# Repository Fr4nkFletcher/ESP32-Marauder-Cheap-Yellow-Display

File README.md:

# Marauder 1.4.3 for CYD 4.0" E32R40T

- Add support for ESP32-4848S040 4.0" ST7796/XPT2046 Resistive Touch (E32R40T)
- Portrait and landscape touch calibration measured on E32R40T hardware
- CYD_40 set as the default active board
- Add `User_Setup_cyd40.h` TFT_eSPI configuration for CYD_40

---

## Requirements

1. A compatible CYD module (see [Compatibility](#compatibility) section below)
2. A data-capable USB cable
3. *(Optional)* GPS module for enhanced functionality — https://github.com/justcallmekoko/ESP32Marauder/wiki/gps-modification

---

## Installation

### Option 1 — esptool.py (Recommended)

Flash directly from the prebuilt binaries in this repo.

Install esptool if you don't have it:

```
pip install esptool
```

Flash:

```
esptool.py --port /dev/YOURSERIALPORT write_flash \
  0x1000  bins/esp32_marauder.ino.bootloader.bin \
  0x8000  bins/esp32_marauder.ino.partitions.bin \
  0x10000 bins/esp32_marauder_v1_4_3_20260627_cyd40_nogps.bin
```

Replace the firmware filename with `cyd40_gps.bin` if you have a GPS module wired up.

#### Troubleshooting:

1. Unplug and restart your CYD module
2. Hold `RST`, tap `BOOT`, release `RST` (the screen should go blank)
3. Re-run the flash command

---

### Option 2 — Arduino IDE (Build from Source)

1. Set up your Arduino environment following the [ESP32 Marauder Arduino IDE Setup Guide](https://github.com/justcallmekoko/ESP32Marauder/wiki/arduino-ide-setup)
2. Update your platform.txt
3. Add the necessary libraries to your Arduino libraries folder
4. Set the upload speed to `115200`
5. In `configs.h`, uncomment the `#define` for your board (default is `CYD_40`)
6. Upload to your CYD module

---

## Compatibility

The following boards are supported. The **4.0" E32R40T** is the default in this fork — for any other board, comment out `#define CYD_40` in `configs.h` and uncomment your board's define.

- **[4.0" Resistive Touch E32R40T](https://www.amazon.com/dp/B0FGJJ24S1)** ← default in this fork
- [1.9" ESP32-S3 No Touch](https://www.aliexpress.us/item/3256807423694742.html)
- [2.4" Capacitive Touch](https://a.co/d/bTSoo9Z)
- [2.4" Resistive Touch](https://a.co/d/fhM7s0J)
- [2.4" Resistive Touch Guition](https://www.aliexpress.us/item/3256806436471011.html)
- [2.8" Resistive MicroUSB-only](https://amazon.com/dp/B0BVFXR313)
- [2.8" Resistive MicroUSB/Type-C 2USB](https://amazon.com/dp/B0CLR7MQ91)
- [3.2" Resistive Touch](https://www.aliexpress.us/item/3256806436888726.html)
- [3.2" Capacitive Touch](https://a.co/d/faB7oVU)
- [3.5" Resistive Touch](https://a.co/d/cxUc73a)
- [3.5" Capacitive Touch](https://a.co/d/2PFDlvL)

No hardware modifications required.

---

## GPS Functionality

GPS is supported via the 4-pin connector near the MicroUSB port. For compatible hardware, refer to the [official wiki](https://github.com/justcallmekoko/ESP32Marauder/wiki/gps-modification).

| GPS | -> | CYD |
|-----|:--:|-----|
| VCC | -> | VIN |
| GND | -> | GND |
| TX  | -> | TX  |
| RX  | -> | RX  |

Note: On 2.4" and 3.5" models swap RX/TX

---

## Example Usage

After flashing, you'll boot into the Marauder interface. Refer to the [ESP32 Marauder Wiki](https://github.com/justcallmekoko/ESP32Marauder/wiki) for detailed usage instructions.

---

## Disclaimer

This project is for educational purposes only. Always obtain proper authorization before testing on networks you don't own or have explicit permission to test.

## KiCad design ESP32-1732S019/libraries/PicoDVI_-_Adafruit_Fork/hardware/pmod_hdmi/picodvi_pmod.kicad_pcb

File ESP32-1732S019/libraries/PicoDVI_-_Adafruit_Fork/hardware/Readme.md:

PicoDVI Hardware
================

This directory contains schematics and layout files

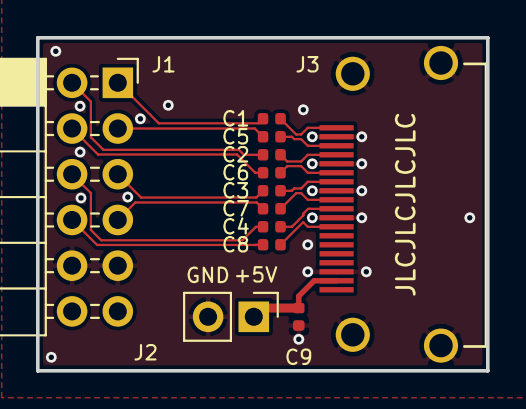
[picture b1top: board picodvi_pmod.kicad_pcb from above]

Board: 2 copper layers, 25.0 x 18.5 mm, 12 parts (0 on the bottom side), 19 nets.

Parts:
C1, C2, C3, C4, C5, C6, C7, C8, C9: 220n; C_0402_1005Metric
J1: 02x06; PinSocket_2x06_P2.54mm_Horizontal
J2: Conn_01x02; PinHeader_1x02_P2.54mm_Vertical
J3: HDMI_A; HDMI-SS-53000

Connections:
+3V3: J1.11, J1.12
+5V: C9.2, J2.1, J3.18
/CK+: C4.1, J3.10
/CK-: C8.1, J3.12
/D0+: C3.1, J3.7
/D0-: C7.1, J3.9
/D1+: C2.1, J3.4
/D1-: C6.1, J3.6
/D2+: C1.1, J3.1
/D2-: C5.1, J3.3
/PMOD_CK+: C4.2, J1.6
/PMOD_CK-: C8.2, J1.8
/PMOD_D0+: C3.2, J1.5
/PMOD_D0-: C7.2, J1.7
/PMOD_D1+: C2.2, J1.2
/PMOD_D1-: C6.2, J1.4
/PMOD_D2+: C1.2, J1.1
/PMOD_D2-: C5.2, J1.3
GND: C9.1, J1.9, J1.10, J2.2, J3.2, J3.5, J3.8, J3.11, J3.17, J3.SH

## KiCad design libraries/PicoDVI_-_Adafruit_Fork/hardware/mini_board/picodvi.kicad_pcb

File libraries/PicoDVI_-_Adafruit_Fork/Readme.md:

PicoDVI - Adafruit Fork for Arduino IDE + Adafruit_GFX compatibility
====================================================================
(Original Readme content follows later)

Implements a few framebuffer types to which Adafruit_GFX drawing operations
can be made; not every permutation PicoDVI is capable of, but a useful subset.

WARNING: all video modes require overclocking (performed automatically at
run-time, nothing to select), occasionally over-volting (optionally selected
in sketch code), and higher resolutions may require reducing the QSPI clock
rate (Tools menu in future arduino-pico release). The RP2040 microcontroller
is being run WAY beyond spec and there is a VERY SMALL BUT NONZERO
POSSIBILITY OF PERMANENT DAMAGE. Please see LICENSE file; usual software
disclaimers about liability apply, user accepts risk.

Requires Earle Philhower III RP2040 Arduino core (not the "official" Arduino
RP2040 core).

Changes vs main PicoDVI repo:
- Add library.properties file, src and examples directories per Arduino
requirements.
- A full copy of software/libdvi is made in src (originally was soft-linked but Arduino Library Manager does not approve). If any updates are made in the original PicoDVI libdvi directory, copy them here!
- The file dvi_serialiser.pio.h, normally not part of the distribution and
generated during the Pico SDK build process, is provided here for Arduino
build to work. If any changes are made in dvi_serialiser.pio (either here
or by bringing in updates from upstream code), this header will need to be
regenerated.
- extern "C" around most function defs, to be linkable with C++ (Arduino).
- A couple compile-time constants have been changed to run-time configurable
because some color and resolution things aren't known until a constructor is
called: dvi_vertical_repeat and dvi_monochrome_tmds.
- DVI_1BPP_BIT_REVERSE is switched '1' by default (to work with bit order
used by GFXcanvas1 object). Pico SDK-built examples using 1-bit mode are
fixed by changing the corresponding CMakeLists.txt files to set this to 0.
Font data has had bit order reversed to match this layout.

All files from the PicoDVI repo are kept even if not used in this build
(e.g. apps and assets directories, among others) so same repo can still be
used via Pico SDK if desired.

Original Readme content:
=======
RP2350 PicoDVI Preview
======================

Changes from the public GitHub version:

* All Arm assembly in `libdvi` has been ported to RISC-V and tuned for Hazard3
* Some of the existing Arm assembly in `libdvi` has been tweaked for better performance on Cortex-M33
* RGB encode now uses the SIO TMDS encoders by default on RP2350 (can be disabled by defining `DVI_USE_SIO_TMDS_ENCODE=0` -- see `software/libdvi/dvi_config_defs.h`)
* Much of the Arm assembly in `libsprite` has been ported to RISC-V -- enough to run the stock demos

Build instructions:

```bash
cd software
mkdir build
# PICO_PLATFORM can also be rp2350-riscv
# List of DVI configs is in software/include/common_dvi_pin_configs.h
cmake -DPICO_SDK_PATH=/path/to/sdk -DPICO_PLATFORM=rp2350 -DPICO_COPY_TO_RAM=1 -DDVI_DEFAULT_SERIAL_CONFIG=pico_sock_cfg ..
make -j$(nproc)
# Then flash a binary, e.g.:
cp apps/tiles_and_sprites/tiles_and_sprites.uf2
```

If you plan to run the `vista` demo, then note that there are now two UF2 data files, `software/assets/vista_data_rp2040.uf2` and `software/assets/vista_data_rp2350.uf2`. The only difference is the family IDs: the first can be dragged on RP2040 and on RP2350 A0, and the second can be dragged on RP2350 A1 and later.

The following is the original RP2040 writeup:

Bitbanged DVI on the RP2040 Microcontroller
===========================================

*640x480 RGB565 image, 640x480p 60 Hz DVI mode. 264 kB SRAM, 2x Cortex-M0+, system clock 252 MHz*

Quick links:

[Board Schematic](hardware/board/picodvi.pdf)

[Software Readme and Example Photos](software/)

About this Project
-----------------

This project stems from a stupid idea I had during RP2040 bringup. I couldn't convince myself the idea was too stupid to work, so I took a leap of faith on it, and the results are documented here.

RP2040 was designed to run at 133 MHz, but we found (without too much surprise) that typical silicon can be pushed further. In fact, there was overlap between the maximum system clock, and the TMDS bit clocks of slower DVI video modes. We had done great stuff with VGA on the FPGA platform, which ran at 48 MHz, but wouldn't it be absurd and wonderful to connect your microcontroller straight to an HD TV with no other electronics in between? This seemed unlikely to work out, but I stayed up at night playing around with assembly loops, and I could not convince myself that DVI was out of reach. Everything seemed to fit:

- With some of the core-local hardware on RP2040, and a neat encoding trick, I could do pixel-doubled TMDS encode on-the-fly using around 60% of an M0+ (running at 252 MHz, for 640x480p 60 Hz DVI)
- PIO can yeet out data streams at system clock frequency, and drive a 1/10th rate clock on the side, with pretty minimal programming
- Some of the DMA features are help with putting together the sync/blanking patterns on the fly, rather than having the patterns flat in memory
- With the second processor utterly unencumbered, you can render some pretty graphics to put on your DVI display. There is even enough RAM for a QVGA framebuffer!

The greatest unknown was driving 252 Mbps serial through the general-purpose digital pads (especially *differential* serial, emulated with two single-ended pads). By this point I was utterly driven and consumed by the need to find out if DVI could work, so I laid out a board over a few evenings after work.

The Rev A board uses a slightly cursed coupling circuit I first saw (and used) on the ULX3S FPGA board, which just connects 3V3 IOs straight into the HDMI socket through some coupling caps.

Those who understand the TMDS physical layer are probably screaming, but I was fine, because I did not read the electrical section of the spec until after I got this board working. Then I screamed. Before the boards arrived I did some debugging, with these two strategies:

- Run the entire system at 12 MHz (crystal freq), so that the signals are probeable, but the relative speed of IO, DMA and CPUs is the same. This makes sure my code can keep the PIO state machines fed with data
- Swap in an alternate PIO program which outputs 10 bit UART data frames instead of direct serial (a 17% drop in throughput). I could then dump the TMDS stream with a logic analyser, and examine and parse it on my machine

I also tried out my slightly harebrained TMDS encoding scheme, which matches the letter but not the spirit of the DVI specification, on an FPGA board with some DVI gateware I wrote for a previous weekend project. This confirmed that the principle was sound, and that my TV and monitor would have no trouble with the output of the matching software encoder on RP2040, provided the chip could physically shove bits out of the pins fast enough.

Because this is a home project, I didn't touch the HDL sim, and stuck to ARM debug, UART and logic analyser for my debugging. This worked some kinks out of the software, and bringup of the freshly-soldered board was smooth. After swapping the blue and red lanes into the right order -- to which I will say, in my defense, I _consistently_ thought the blue+sync lane was lane 2 -- I had a clean RGB565 QVGA 60 Hz static image on my monitor.

Improved Output Circuit
-----------------------

After reading the TMDS electrical section of the DVI spec, and staring quietly out the window for a while, wondering how this board *ever* worked, I rethought the output circuit. Eight capacitors was clearly not the way to go -- what I really needed was eight *resistors*. That's what I call a DVI PHY.

I also revised my earlier approach of "turn all the GPIOs up to 11", and reduced the pad drive and slew. At work on Monday, a colleague agreed it would be a great idea to plug my microcontroller monstrosity into the scope setup we use for 4k HDMI testing. Here are the results at VGA 60 Hz (252 Mbps):

I was sitting on the other side of the lab while he was running the test, and when the eye mask appeared he just said "do you wanna see something funny".

A clean bill of health! We also tried 720p30 (372 Mbps), which requires overvoltage on typical silicon (something you can do with one register write on RP2040):

Honestly, this has shaken me. This is a silly amount of bandwidth for a tiny little microcontroller.

Although it passes the eye mask and a few other tests, this circuit is not fully compliant with the DVI spec. In particular, our logic `1` is not quite right, due to the CMOS drive on the GPIOs: any more than a \~60 mV mismatch between the Source and Sink +3V3 rails will push our high-level offset outside of the +- 10 mV allowed by the spec. This is a real nitpick, because a *differential* receiver is unlikely to care about a 10 mV *commmon mode* offset, but still -- it is out of spec. A better circuit could use a fast Si diode and a smaller resistor value, e.g. 220 ohm, so that the emulated CML output floats on the sink's +3V3 supply when we output our 3V3 CMOS high level, but still sinks the requisite 10 mA when driving low.

That said, it's compliant enough that I can wander around the office and plug it into every monitor I see, and not even _one_ of them explodes (if my manager is reading this -- hi).

Going Further
-------------

Everything we have done is software defined -- there's no video hardware on this chip. That would of course be _silly_ on a microcontroller. Let's list all the hardware resources used to display a pixel-doubled image on screen:

- 3 out of 8 PIO state machines (the DVI code requires these all be on the same PIO instance, of which there are two, with four state machines each)
- 6 out of 12 DMA channels (two per TMDS lane: one for control blocks, one for data)
- 30% of DMA bandwidth and PIO bus endpoint bandwidth
- 60% of CPU cycles on one core, other core 100% free
- Just over 50% of RAM with a QVGA RGB565 image (but RGB332 support is simple enough)
- The PicoDVI board's only HDMI-shaped socket

Hmm. All of these numbers are less than half of the total, and everything else is software. It's a shame there's only one socket I can put an HDMI cable in. I mean, I guess I _do_ have these adorable PMOD-DVI adapters that I keep plugging into FPGA boards and getting away with it:

Oh. Maybe? It fits...

I guess the jig is up at this point, because of course I wouldn't post something so daft-looking if it didn't work:

[The code is here.](software/apps/dual_display/main.c)

Example Apps
------------

The [software readme](software/) has some example apps which put the DVI library through its paces, with pictures for some of the fun ones. I won't duplicate that content here.

Encoding TMDS
-------------

DVI uses an encoding scheme called TMDS during the video periods. 8 data bits are represented by a 10 bit TMDS symbol, which is serialised at 10x the pixel clock. 3 lanes transfer 24 bits of data per pixel clock, which for our purposes is one pixel. TMDS is DC-balanced, although DVI as a whole is *not* DC-balanced on all lanes, due to the control symbol encoding. The algorithm given in the DVI spec is quite fussy, and you are supposed to match its output exactly. It tracks running disparity with a counter, and optionally inverts symbols to bound the disparity, with some tie-break rules for 0-balance symbols.

Key fact about TMDS: if the current running disparity is 0, and you encode data `x` followed by data `x ^ 0x01`, this produces a pair of TMDS symbols with 0 net parity. If you manipulate the input data in this way -- duplicating the pixels, and twiddling the LSB -- TMDS becomes *stateless*, because the running disparity is defined to be 0 at the start of each video period, and returns to 0 after each duplicated pixel pair.

If we have a half-resolution scanline buffer, and are only interested in 7 or fewer bits of significance for each colour channel, we can encode this with a lookup table, where each entry is two TMDS symbols with net balance 0. The toggling of the LSB with each output pixel is not noticeable.

Great. LUTs are fast. On a Cortex-M0+, though, they are not *that* fast. Each load/store is 2 cycles, and we end up spending a surprising amount of time shifting and masking the data. Here is a vaguely plausible loop for encoding one colour channel, compiled with `-O3 -mcpu=cortex-m0plus` on gcc 9 ([Godbolt link](https://godbolt.org/z/q741oK)).

*C*

```
void tmds_encode_16bpp(const uint16_t *pixbuf, uint32_t *tmdsbuf, size_t n_pix, uint16_t chan_mask, unsigned int chan_shift) {
    for (size_t i = 0; i < n_pix; ++i) {
        unsigned int idx = (pixbuf[i] >> chan_shift) & chan_mask;
        tmdsbuf[2 * i] = tmds_table[idx];
        tmdsbuf[2 * i + 1] = tmds_table[idx + 1];
    }
}
```

*ARMv6M*

```
tmds_encode_16bpp(unsigned short const*, unsigned long*, unsigned int, unsigned short, unsigned int):
        push    {r4, r5, r6, r7, lr}
        ldr     r7, [sp, #20]
        cmp     r2, #0
        beq     .L1
        lsls    r2, r2, #3
        ldr     r5, .L6
        adds    r2, r1, r2

.L4:
        ldrh    r4, [r0]     ; 2 cyc
        adds    r0, r0, #2   ; 1 cyc
        asrs    r4, r4, r7   ; 1 cyc
        ands    r4, r3       ; 1 cyc

        lsls    r6, r4, #2   ; 1 cyc
        ldr     r6, [r5, r6] ; 2 cyc
        adds    r4, r4, #1   ; 1 cyc
        str     r6, [r1]     ; 2 cyc

        lsls    r4, r4, #2   ; 1 cyc
        ldr     r4, [r5, r4] ; 2 cyc
        str     r4, [r1, #4] ; 2 cyc

        adds    r1, r1, #8   ; 1 cyc
        cmp     r2, r1       ; 1 cyc
        bne     .L4          ; 2 cyc if taken
.L1:
        pop     {r4, r5, r6, r7, pc}
```

Focusing on the loop starting at `.L4`, this is a surprisingly literal translation -- first load a pixel, bump the pointer, mask and shift (5 cycles). Next transfer a pixel from the LUT to the output buffer (5 cycles) while bumping the LUT index (1 cycle), transfer the second pixel (5 cycles), do a little bookkeeping and branch back to the start (4 cycles). Each loop takes 20 cycles, and encodes one colour channel of 2 output pixels.

We must output a pixel once per 10 system clock cycles (as the system runs at the TMDS bit clock), and since we are doubling pixels horizontally we may as well double vertically too, by using each encoded buffer twice. Taking horizontal blanking into account (1:4 ratio at VGA), we would spend 1.2 of our two cores on TMDS encode, and have 0.8 cores left to generate DVI timing and render graphics.

The compiler has messed up here (or perhaps I have unwittingly constrained it to produce bad code by writing shoddy C), and we can save 4 cycles right off the bat with better instruction selection:

```
.L4:
        ldrh    r4, [r0]     ; 2 cyc
        adds    r0, r0, #2   ; 1 cyc
        asrs    r4, r4, r7   ; 1 cyc
        ands    r4, r3       ; 1 cyc

        lsls    r4, r4, #2   ; 1 cyc
        ldr     r6, [r5, r4] ; 2 cyc
        stmia   r1!, {r6}    ; 2 cyc

        adds    r4, r4, #4   ; 1 cyc
        ldr     r6, [r5, r4] ; 2 cyc
        stmia   r1!, {r6}    ; 2 cyc

        cmp     r2, r1       ; 1 cyc
        bne     .L4          ; 2 cyc if taken
```

But this is still painfully slow -- it wouldn't even fit on one core. Some avenues for improvement:

- Use a word load to fetch two input pixels at once, so we can amortise the load cost, and some of the shift/mask cost
- Use larger `ldmia` and `stmia` on the LUT to squeeze more memory bandwidth out of the M0+ (`ldr` is 2 cycles and `ldmia` is n + 1)
- Use the interpolators on RP2040 to accelerate address generation

The interpolator is a fun piece of hardware for accelerating fixed point arithmetic. Note: "interpolator" is a working title which we will definitely not forget to change to something better before launch. The _original_ plan was a simple configurable 2D phase accumulator that we could use to play Super Mario Kart on the FPGA platform at 48 MHz. Sadly, that game port never materialised, not least because we couldn't publish it. After a lot of back and forth between hardware and software, we realised that making the datapath a little more flexible would go a long way, and this eventually let to the current guise of the interpolator:

Our trick here is loading a one-word pixel pair into one of the accumulators, and configuring the interpolator to extract the correct bits of each pixel, shift them, and add them to a LUT base pointer. The interpolator doesn't have a left shift (not needed for Super Mario Kart) so for the blue channel (least significant in our RGB565 pixel format) we need to do one left shift per two pixels on the processor, to scale up to the LUT entry size. For the other channels we can use a different loop, without the left shift. Here is the encode loop from `tmds_encode.S`:

```
// r0: Input buffer (word-aligned)
// r1: Output buffer (word-aligned)
// r2: Input size (pixels)
// r3: Left shift amount

decl_func tmds_encode_loop_16bpp_leftshift
	push {r4, r5, r6, r7, lr}
	lsls r2, #3
	add r2, r1
	mov ip, r2
	ldr r2, =(SIO_BASE + SIO_INTERP0_ACCUM0_OFFSET)
	b 2f
.align 2
1:
.rept TMDS_ENCODE_UNROLL
	ldmia r0!, {r4}             ; 2 cyc
	lsls r4, r3                 ; 1 cyc
	str r4, [r2, #ACCUM0_OFFS]  ; 1 cyc
	ldr r4, [r2, #PEEK0_OFFS]   ; 1 cyc
	ldmia r4, {r4, r5}          ; 3 cyc
	ldr r6, [r2, #PEEK1_OFFS]   ; 1 cyc
	ldmia r6, {r6, r7}          ; 3 cyc
	stmia r1!, {r4, r5, r6, r7} ; 5 cyc
.endr
2:
	cmp r1, ip                  ; 1 cyc
	bne 1b                      ; 2 cyc if taken
	pop {r4, r5, r6, r7, pc}
```

Assuming `TMDS_ENCODE_UNROLL=1`, each loop iteration takes 20 cycles, and produces 4 output pixels. Taking the lack of left shift for red and green into account, this works out to 58% of a core to do TMDS encode, which is just over 2x faster than the compiled LUT loop. We can get another 10 or 15% performance by increasing `TMDS_ENCODE_UNROLL`.

We handle 8bpp pixels in a similar way, but use both interpolators -- one to extract pixels 0 and 1 from the loaded word, and one for pixels 2 and 3. 8bpp encode is slightly faster than 16bpp encode, because we get four pixels for each load from the pixel buffer.

It is just barely possible to do full resolution encode, which is what is shown off in the first image at the top of this Readme. The code is awful, go check it out if you hate yourself.

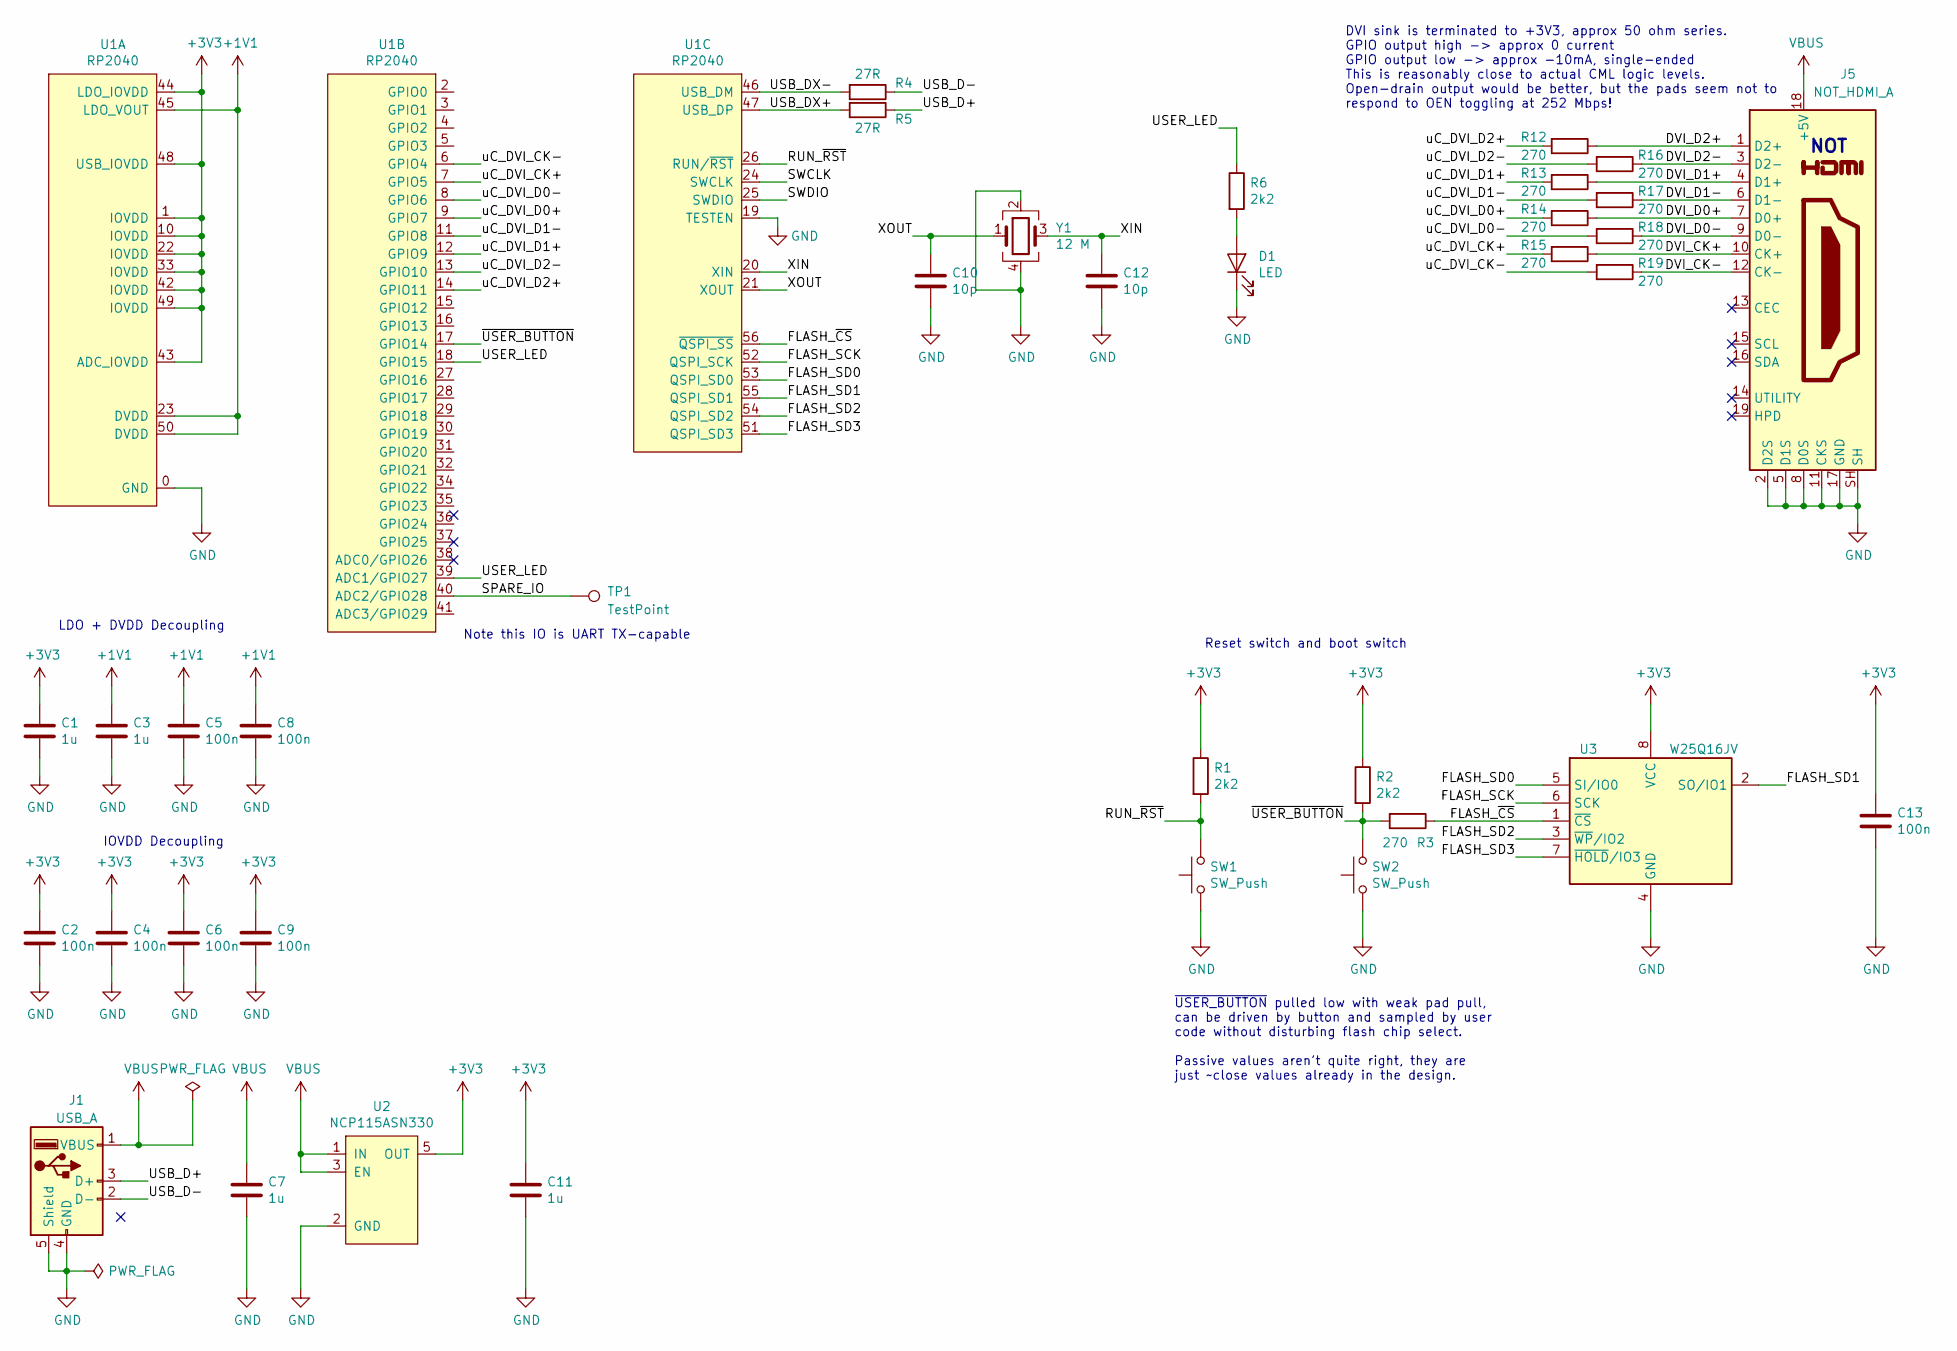
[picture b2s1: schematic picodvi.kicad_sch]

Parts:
C1, C3, C7, C11: 1u; C_0402_1005Metric
C2, C4, C5, C6, C8, C9, C13: 100n; C_0402_1005Metric
C10, C12: 10p; C_0402_1005Metric
D1: LED; LED_0805_2012Metric
J1: USB_A; USB_A_PLUG_PCB
J5: NOT_HDMI_A; HDMI-SS-53000
R1, R2, R6: 2k2; R_0402_1005Metric
R3, R12, R13, R14, R15, R16, R17, R18, R19: 270; R_0402_1005Metric
R4, R5: 27R; R_0402_1005Metric
SW1, SW2: SW_Push; SW_SPST_PTS815
TP1: TestPoint; TestPoint_Pad_1.0x1.0mm
U1: RP2040; QFN-56_EP_7x7_Pitch0.4mm
U2: NCP115ASN330; SOT-23-5_HandSoldering
U3: W25Q16JV; WSON-8-1EP_6x5mm_P1.27mm_EP3.4x4mm
Y1: 12 M; Crystal_SMD_3225-4Pin_3.2x2.5mm

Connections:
+1V1: C3.1, C5.1, C8.1, U1.23 (DVDD), U1.45 (LDO_VOUT), U1.50 (DVDD)
+3V3: C1.1, C2.1, C4.1, C6.1, C9.1, C11.1, C13.1, R1.1, R2.1, U1.1 (IOVDD), U1.10 (IOVDD), U1.22 (IOVDD), U1.33 (IOVDD), U1.42 (IOVDD), U1.43 (ADC_IOVDD), U1.44 (LDO_IOVDD), U1.48 (USB_IOVDD), U1.49 (IOVDD), U2.5 (OUT), U3.8 (VCC)
/DVI_CK+: J5.10 (CK+), R15.1
/DVI_CK-: J5.12 (CK-), R19.1
/DVI_D0+: J5.7 (D0+), R14.1
/DVI_D0-: J5.9 (D0-), R18.1
/DVI_D1+: J5.4 (D1+), R13.1
/DVI_D1-: J5.6 (D1-), R17.1
/DVI_D2+: J5.1 (D2+), R12.1
/DVI_D2-: J5.3 (D2-), R16.1
/FLASH_SCK: U1.52 (QSPI_SCK), U3.6 (SCK)
/FLASH_SD0: U1.53 (QSPI_SD0), U3.5 (SI/IO0)
/FLASH_SD1: U1.55 (QSPI_SD1), U3.2 (SO/IO1)
/FLASH_SD2: U1.54 (QSPI_SD2), U3.3 (~WP~/IO2)
/FLASH_SD3: U1.51 (QSPI_SD3), U3.7 (~HOLD~/IO3)
/FLASH_~CS~: R3.1, U1.56 (~QSPI_SS~), U3.1 (~CS)
/RUN_~RST~: R1.2, SW1.2, U1.26 (RUN/~RST~)
/SPARE_IO: TP1.1, U1.40 (ADC2/GPIO28)
/SWCLK: U1.24 (SWCLK)
/SWDIO: U1.25 (SWDIO)
/USB_D+: J1.3 (D+), R5.1
/USB_D-: J1.2 (D-), R4.1
/USB_DX+: R5.2, U1.47 (USB_DP)
/USB_DX-: R4.2, U1.46 (USB_DM)
/USER_LED: R6.1, U1.18 (GPIO15), U1.39 (ADC1/GPIO27)
/XIN: C12.1, U1.20 (XIN), Y1.3
/XOUT: C10.1, U1.21 (XOUT), Y1.1
/uC_DVI_CK+: R15.2, U1.7 (GPIO5)
/uC_DVI_CK-: R19.2, U1.6 (GPIO4)
/uC_DVI_D0+: R14.2, U1.9 (GPIO7)
/uC_DVI_D0-: R18.2, U1.8 (GPIO6)
/uC_DVI_D1+: R13.2, U1.12 (GPIO9)
/uC_DVI_D1-: R17.2, U1.11 (GPIO8)
/uC_DVI_D2+: R12.2, U1.14 (GPIO11)
/uC_DVI_D2-: R16.2, U1.13 (GPIO10)
/~USER_BUTTON~: R2.2, R3.2, SW2.2, U1.17 (GPIO14)
GND: C1.2, C2.2, C3.2, C4.2, C5.2, C6.2, C7.2, C8.2, C9.2, C10.2, C11.2, C12.2, C13.2, D1.1 (K), J1.4 (GND), J1.5 (Shield), J5.2 (D2S), J5.5 (D1S), J5.8 (D0S), J5.11 (CKS), J5.17 (GND), J5.SH, SW1.1, SW2.1, U1.0 (GND), U1.19 (TESTEN), U2.2 (GND), U3.4 (GND), Y1.2, Y1.4
unnamed: D1.2 (A), R6.2
VBUS: C7.1, J1.1 (VBUS), J5.18 (+5V), U2.1 (IN), U2.3 (EN)

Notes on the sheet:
LDO + DVDD Decoupling
IOVDD Decoupling
Note this IO is UART TX-capable
~USER_BUTTON~ pulled low with weak pad pull, can be driven by button and sampled by user code without disturbing flash chip select. Passive values aren't quite right, they are just ~~close values already in the design.
DVI sink is terminated to +3V3, approx 50 ohm series. GPIO output high -> approx 0 current GPIO output low -> approx -10mA, single-ended This is reasonably close to actual CML logic levels. Open-drain output would be better, but the pads seem not to respond to OEN toggling at 252 Mbps!
Reset switch and boot switch
NOT

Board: 4 copper layers, 37 parts (32 on the bottom side), 37 nets, no tracks yet.

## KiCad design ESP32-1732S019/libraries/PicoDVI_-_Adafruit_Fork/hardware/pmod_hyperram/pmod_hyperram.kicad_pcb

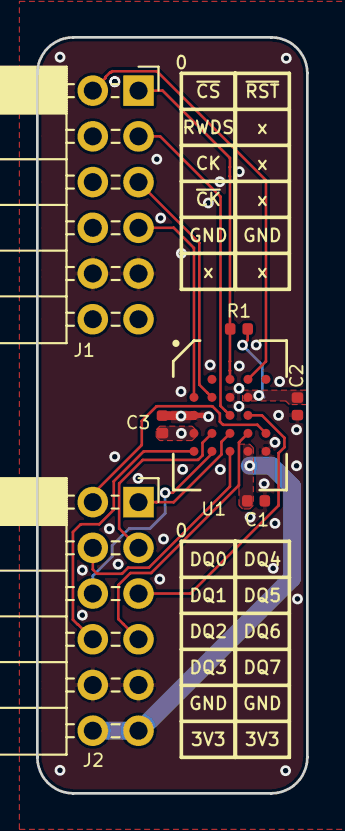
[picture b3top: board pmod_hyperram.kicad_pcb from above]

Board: 2 copper layers, 15.0 x 42.0 mm, 7 parts (0 on the bottom side), 15 nets.

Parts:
C1, C2, C3: 100n; C_0402_1005Metric
J1, J2: 2.54mm_2x6; PinSocket_2x06_P2.54mm_Horizontal
R1: 4k7; R_0402_1005Metric
U1: S70KS128

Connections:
+3V3: C1.1, C2.1, C3.1, J1.11, J1.12, J2.11, J2.12, R1.1, U1.B4, U1.D1, U1.E4
/CK: J1.5, U1.B2
/DQ0: J2.1, U1.D3
/DQ1: J2.3, U1.D2
/DQ2: J2.5, U1.C4
/DQ3: J2.7, U1.D4
/DQ4: J2.2, U1.D5
/DQ5: J2.4, U1.E3
/DQ6: J2.6, U1.E2
/DQ7: J2.8, U1.E1
/RWDS: J1.3, U1.C3
/~CK~: J1.7, U1.B1
/~CS~: J1.1, R1.2, U1.A3
/~RST~: J1.2, U1.A4
GND: C1.2, C2.2, C3.2, J1.9, J1.10, J2.9, J2.10, U1.B3, U1.C1, U1.E5

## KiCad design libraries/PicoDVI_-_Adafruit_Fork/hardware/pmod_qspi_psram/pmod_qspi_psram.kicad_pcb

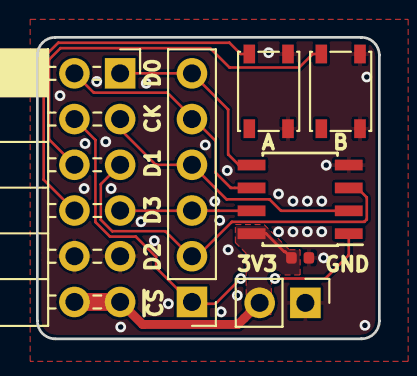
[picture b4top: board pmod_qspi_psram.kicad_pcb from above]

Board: 2 copper layers, 19.0 x 16.8 mm, 7 parts (0 on the bottom side), 10 nets.

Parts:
C1: 100n; C_0402_1005Metric
J1: 2.54mm_2x06; PinSocket_2x06_P2.54mm_Horizontal
J2: Conn_01x06; PinHeader_1x06_P2.54mm_Vertical
J3: Conn_01x02; PinHeader_1x02_P2.54mm_Vertical
SW1, SW2: SW_Push; SW_SPST_PTS815
U1: LY68L6400; SOIC-8_3.9x4.9mm_P1.27mm

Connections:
+3V3: C1.1, J1.11, J1.12, J3.2, U1.8
/BUTTON_A: J1.8, SW1.1
/BUTTON_B: J1.6, SW2.1
/SCK: J1.2, J2.5, U1.6
/SD0: J1.1, J2.6, U1.5
/SD1: J1.3, J2.4, U1.2
/SD2: J1.5, J2.2, U1.3
/SD3: J1.7, J2.3, U1.7
/~CS~: J1.4, J2.1, U1.1
GND: C1.2, J1.9, J1.10, J3.1, SW1.2, SW2.2, U1.4

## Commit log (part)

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2024-03-20 Removed pwnagotchi sniff from GPS enabled builds
2024-03-24 Create img directory
2024-03-24 Uploaded antenna mod image
2024-03-24 Uploaded antenna mod images
2024-03-24 AntennaMod.md tutorial
2024-04-02 Create test
2024-04-02 Added favicons because why not
2024-04-02 Create serial_terminal
2024-04-02 Added a webserial terminal
2024-04-02 Serial Terminal
2024-04-02 Added serial terminal
2024-04-23 Updated webflash instructions
2024-04-23 Webflash update
2024-04-26 0.13.10 update
2024-04-26 Marauder v0.13.10 update
2024-04-28 Enabled RGB LED for builds w/o GPS
2024-04-28 Enabled the RGB LED for builds w/o GPS
2024-04-28 RGB LED enabled for builds w/o GPS
2024-05-02 UI improvements
2024-05-02 Update configs.h to display intenal battery status
    I've added an internal charging,boost module and a 2200mAh battery. Although i do have over discharge protection on it, i'd still like to be able to see a battery indicator of some sort.
2024-06-28 v1.0.0 update
2024-06-28 v1 update
2024-08-06 fix logo
2024-08-06 just a little here, a little there
2024-08-06 web flasher notes
2024-08-15 Clean up old webserial files
2024-08-15 Updated bins
2024-08-23 web flasher info
2024-08-28 idk why
2024-09-03 wroom-32u mod
2024-09-14 hold boot
2024-09-22 f edge
2024-09-28 flash previous versions
2024-10-04 issue 57
    https://github.com/Fr4nkFletcher/ESP32-Marauder-Cheap-Yellow-Display/issues/57
    for @srikeerthis
2024-10-04 issue 57
2024-10-04 more readme edits for @srikeerthis
2024-10-05 yeah
2024-10-06 readme img
2024-10-06 readme
2024-10-21 ESP32-2432S024R 2.4" added
2024-10-27 dont readme
2024-10-27 no read
2024-11-23 v1.1.0 update
2024-11-23 No need
2024-11-23 v1.1.0
2024-11-25 Add Flipper Zero Sniff
2024-11-26 adjust airtag spoofing
2024-11-26 small fix
2024-11-27 more small fixes
2024-11-27 update bins
2024-11-29 log airtag/flipper, more airtag spoof fixes
2024-12-15 v1.2.0
2025-01-10 Add new-line character to username/password in EvilPortal
2025-01-19 Add support for ESP32-3248S035R 3.5" Resistive Touch
    https://github.com/Fr4nkFletcher/ESP32-Marauder-Cheap-Yellow-Display/issues/91
2025-01-19 Added support for ESP32-3248035R 3.5"
2025-01-21 Added alt flashing methods to README.md
2025-01-21 Update flash methods
2025-01-21 Easier to build
2025-01-23 lil this lil that
2025-02-09 v1.2.1
2025-02-15 small fixes
2025-02-16 Add Guition 2.4 support/small fixes
2025-02-16 Add ESP32-2432S024R 3.2" ST7789/XPT2046 support
2025-02-17 Create LICENSE
2025-02-17 Version badge
2025-02-21 last commit badge
2025-02-21 badges
2025-02-21 i cant stop
2025-03-03 small change
2025-03-15 Added ESP32-2432S032C 3.2 Capacitive
2025-03-17 Added ESP32-3248S035C 3.5 Capacitive
2025-03-19 Capacitive small improvements/fixes
2025-03-20 ESP32-2432S024C 2.4 capacitive support added
2025-03-23 README cleanup
2025-03-29 v1.3.1 and many other fixes
2025-04-13 v1.4.2
2025-04-13 Add v1.3.1/v1.4.2 bins to repo folder
2025-04-13 Update working libraries
2025-04-17 v1.4.3
2025-04-18 typo
2025-04-27 ESP32-1732S019N support
2025-05-14 1.9 info
2025-05-18 Add wardriving to 1.9
2025-05-18 test actions
2025-05-18 test actions again
2025-05-18 finish testing workflow ish
2026-04-21 Update README with note on original repository
    Added a note about the original repository.
